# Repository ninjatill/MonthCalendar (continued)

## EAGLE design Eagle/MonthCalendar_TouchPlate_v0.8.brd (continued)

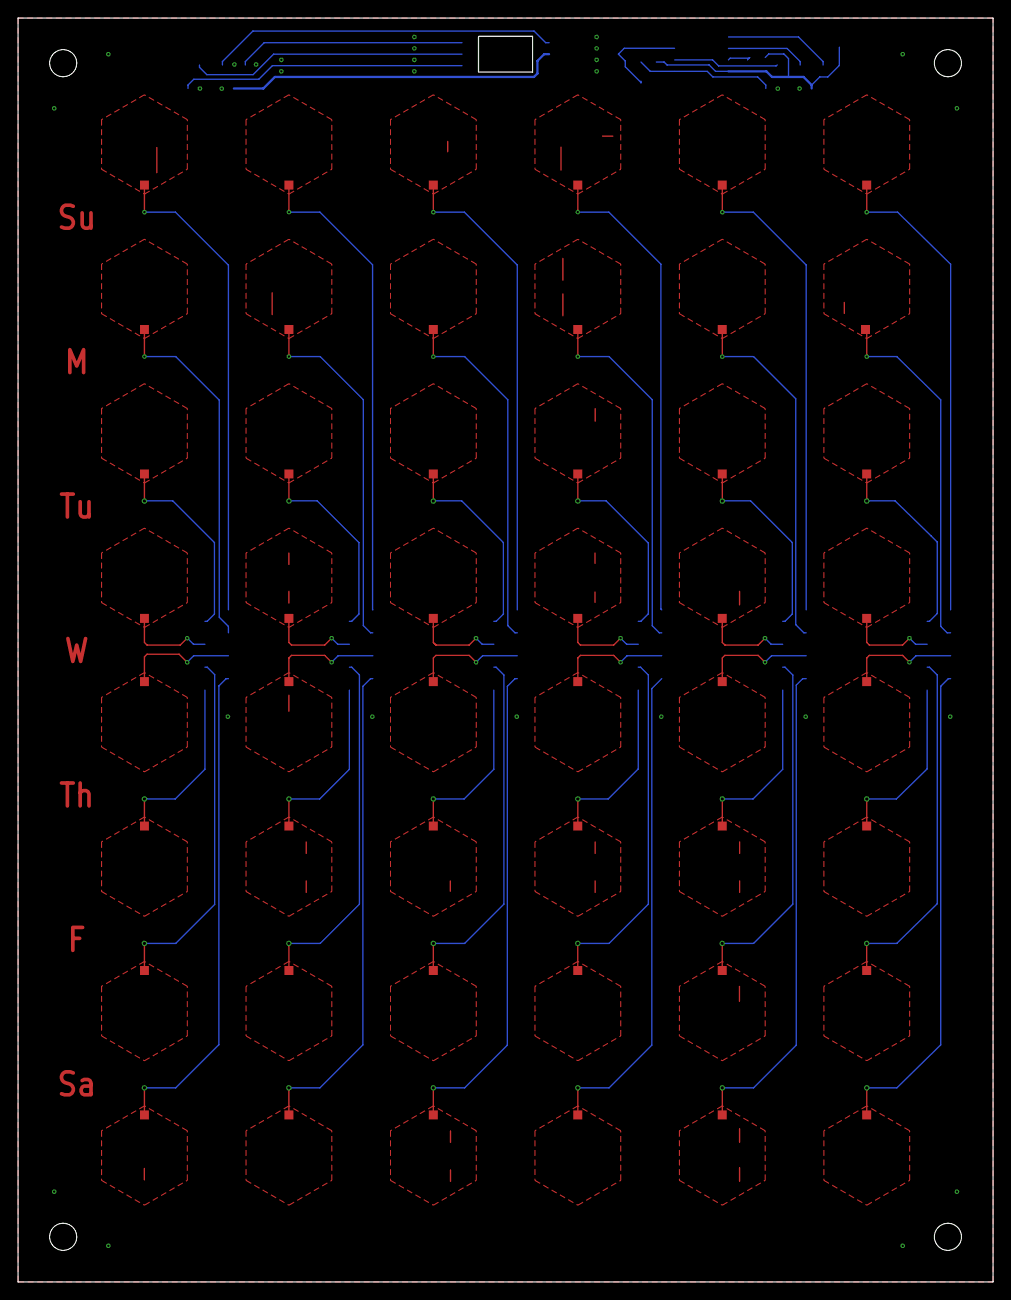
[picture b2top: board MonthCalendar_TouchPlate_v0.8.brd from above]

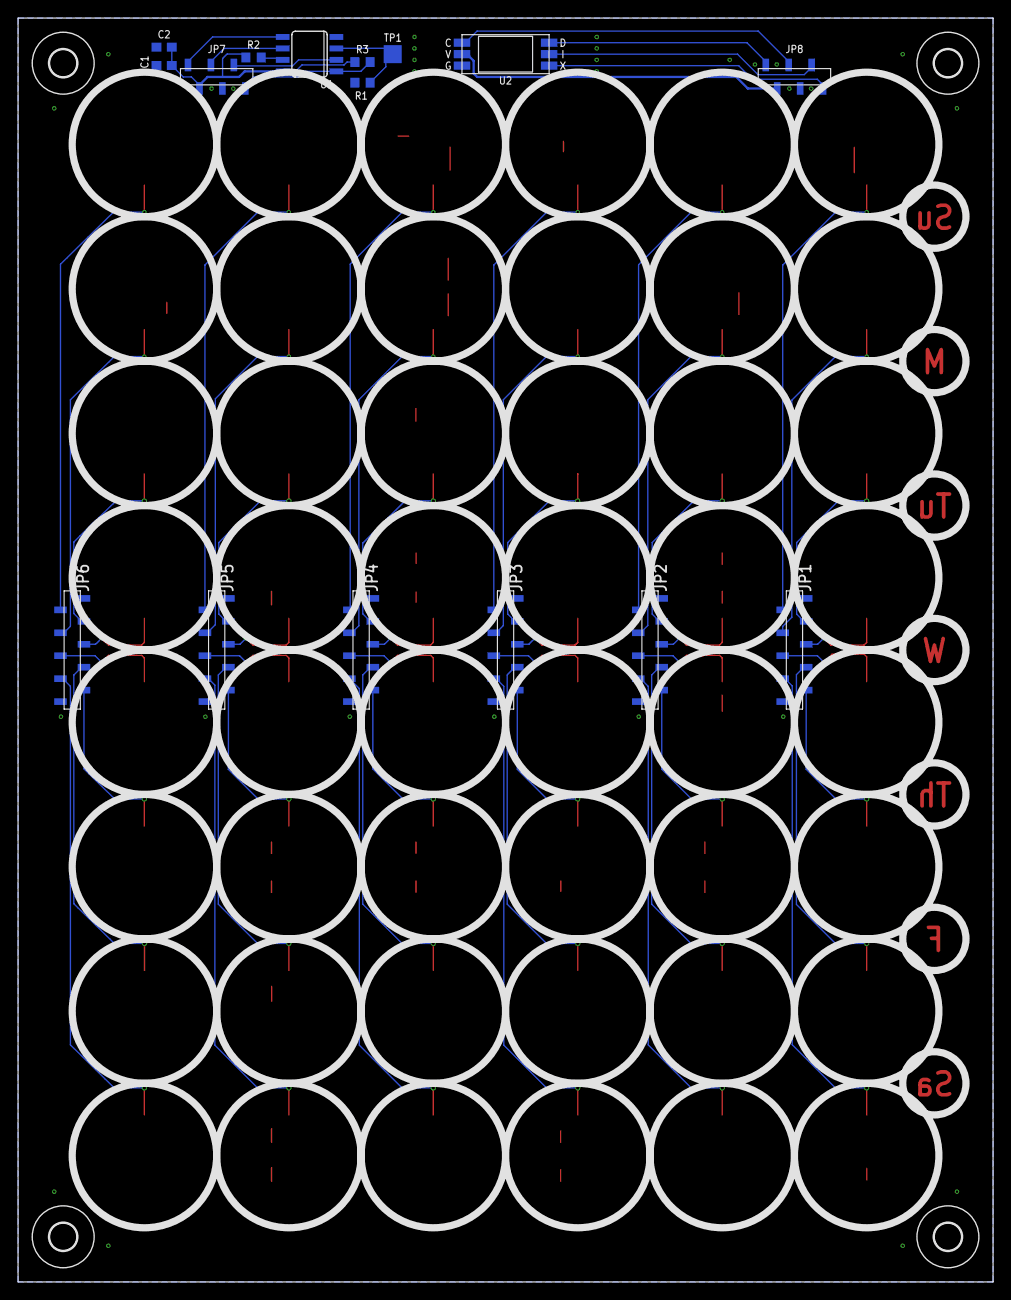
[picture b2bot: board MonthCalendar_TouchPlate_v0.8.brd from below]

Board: 2 copper layers, 108.0 x 140.0 mm, 68 parts (20 on the bottom side), 61 nets.

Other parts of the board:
HOLE_TL: 3,0
U$50, U$51, U$52: 3,0

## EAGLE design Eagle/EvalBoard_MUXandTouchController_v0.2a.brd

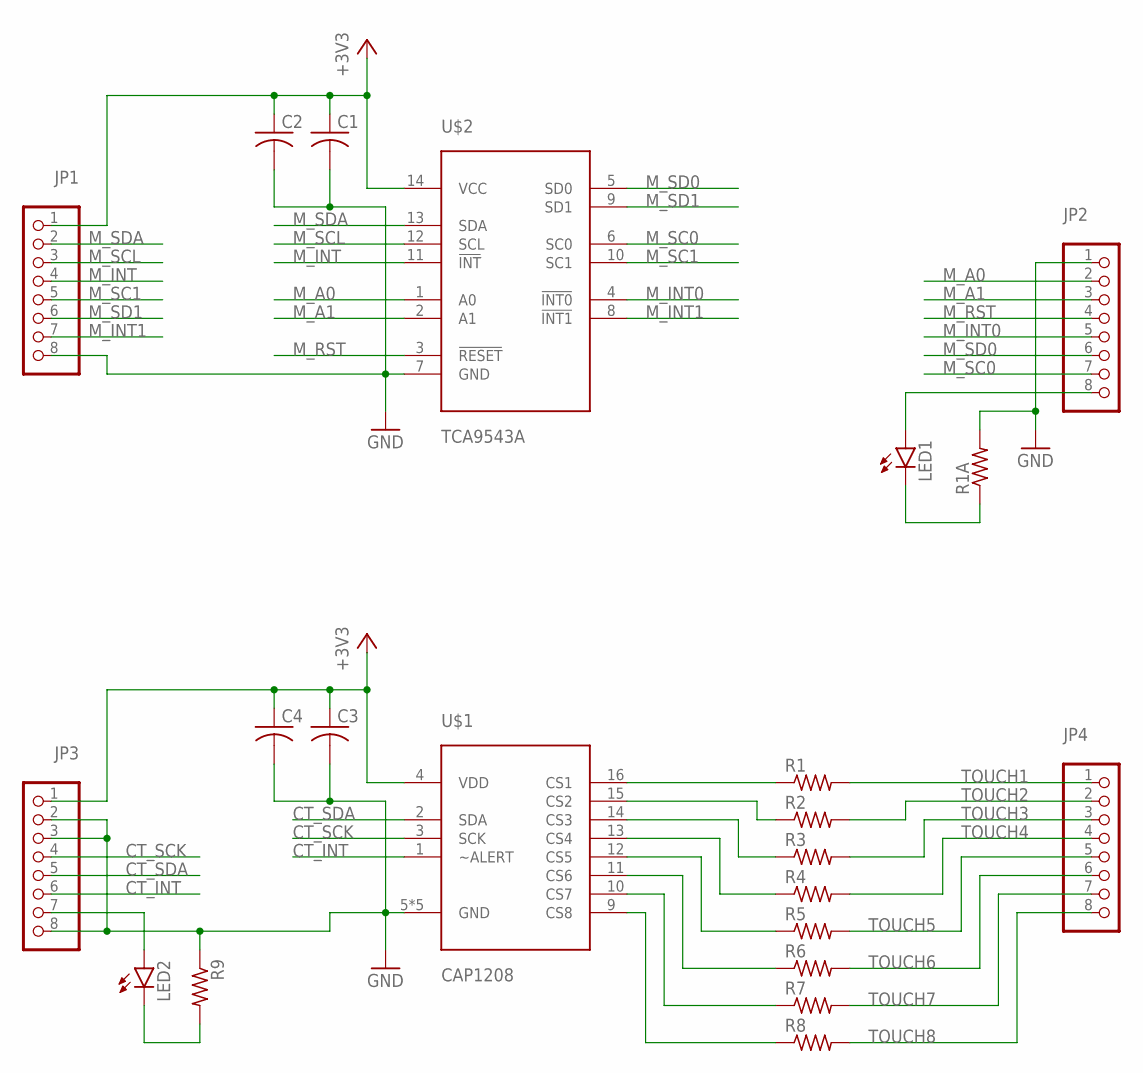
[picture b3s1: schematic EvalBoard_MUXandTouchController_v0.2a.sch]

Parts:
C1, C2, C3, C4: C-USC0603; C0603
JP1, JP2, JP3, JP4: PINHD-1X8BIG; 1X08-BIG
LED1, LED2: LEDCHIP-LED0603; CHIP-LED0603
R1, R1A, R2, R3, R4, R5, R6, R7, R8, R9: R-US_R0603; R0603
U$1: CAP1208; QFN-16-3X3
U$2: TCA9543A; TSSOP-14

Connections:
+3V3: C1.1, C2.1, C3.1, C4.1, JP1.1, JP3.1, U$1.4 (VDD), U$2.14 (VCC)
CT_INT: JP3.6, U$1.1 (~ALERT)
CT_SCK: JP3.4, U$1.3 (SCK)
CT_SDA: JP3.5, U$1.2 (SDA)
GND: C1.2, C2.2, C3.2, C4.2, JP1.8, JP2.1, JP3.2, JP3.3, JP3.8, R1A.2, R9.1, U$1.5 (GND), U$1.6 (GND), U$1.7 (GND), U$1.8 (GND), U$1.PAD (GND), U$2.7 (GND)
M_A0: JP2.2, U$2.1 (A0)
M_A1: JP2.3, U$2.2 (A1)
M_INT: JP1.4, U$2.11 (!INT)
M_INT0: JP2.5, U$2.4 (!INT0)
M_INT1: JP1.7, U$2.8 (!INT1)
M_RST: JP2.4, U$2.3 (!RESET)
M_SC0: JP2.7, U$2.6 (SC0)
M_SC1: JP1.5, U$2.10 (SC1)
M_SCL: JP1.3, U$2.12 (SCL)
M_SD0: JP2.6, U$2.5 (SD0)
M_SD1: JP1.6, U$2.9 (SD1)
M_SDA: JP1.2, U$2.13 (SDA)
unnamed: R1.1, U$1.16 (CS1)
unnamed: JP3.7, LED2.A
unnamed: R2.1, U$1.15 (CS2)
unnamed: LED2.C, R9.2
unnamed: JP2.8, LED1.A
unnamed: LED1.C, R1A.1
unnamed: R3.1, U$1.14 (CS3)
unnamed: R4.1, U$1.13 (CS4)
unnamed: R5.1, U$1.12 (CS5)
unnamed: R6.1, U$1.11 (CS6)
unnamed: R7.1, U$1.10 (CS7)
unnamed: R8.1, U$1.9 (CS8)
TOUCH1: JP4.1, R1.2
TOUCH2: JP4.2, R2.2
TOUCH3: JP4.3, R3.2
TOUCH4: JP4.4, R4.2
TOUCH5: JP4.5, R5.2
TOUCH6: JP4.6, R6.2
TOUCH7: JP4.7, R7.2
TOUCH8: JP4.8, R8.2

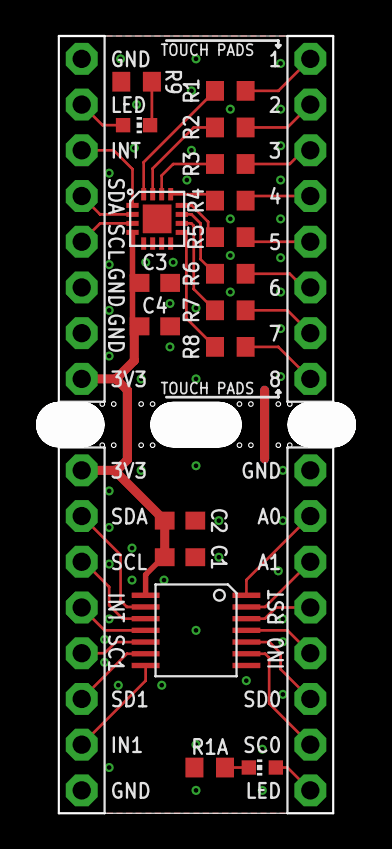
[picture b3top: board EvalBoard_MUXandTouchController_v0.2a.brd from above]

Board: 2 copper layers, 15.2 x 43.2 mm, 22 parts (0 on the bottom side), 37 nets.

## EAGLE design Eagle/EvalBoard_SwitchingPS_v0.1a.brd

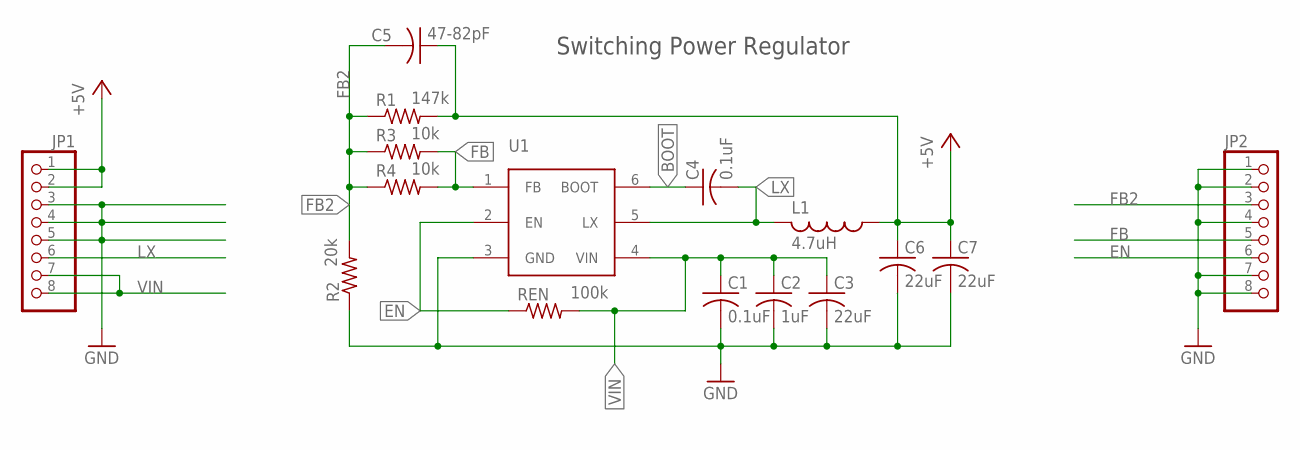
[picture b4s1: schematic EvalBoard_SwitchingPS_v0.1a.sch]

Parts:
C1, C4: 0.1uF; C0603
C2: 1uF; C0603
C3, C6, C7: 22uF; C1206
C5: 47-82pF; C0603
JP1, JP2: PINHD-1X8BIG; 1X08-BIG
L1: 4.7uH; 0207/15
R1: 147k; R0603
R2: 20k; R0603
R3, R4: 10k; R0603
REN: 100k; R0603
U1: RT6255AHGJ6FCT-ND; SOT-23-6

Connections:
+5V: C5.1, C6.1, C7.1, JP1.1, JP1.2, L1.1, R1.2
BOOT: C4.1, U1.6 (BOOT)
EN: JP2.6, REN.1, U1.2 (EN)
FB: JP2.5, R3.2, R4.2, U1.1 (FB)
FB2: C5.2, JP2.3, R1.1, R2.2, R3.1, R4.1
GND: C1.2, C2.2, C3.2, C6.2, C7.2, JP1.3, JP1.4, JP1.5, JP2.1, JP2.2, JP2.4, JP2.7, JP2.8, R2.1, U1.3 (GND)
LX: C4.2, JP1.6, L1.2, U1.5 (LX)
VIN: C1.1, C2.1, C3.1, JP1.7, JP1.8, REN.2, U1.4 (VIN)

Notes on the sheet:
Switching Power Regulator

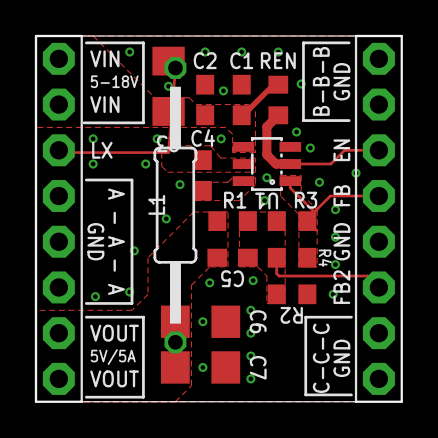
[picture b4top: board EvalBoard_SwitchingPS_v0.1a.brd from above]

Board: 2 copper layers, 20.3 x 20.3 mm, 16 parts (0 on the bottom side), 8 nets.

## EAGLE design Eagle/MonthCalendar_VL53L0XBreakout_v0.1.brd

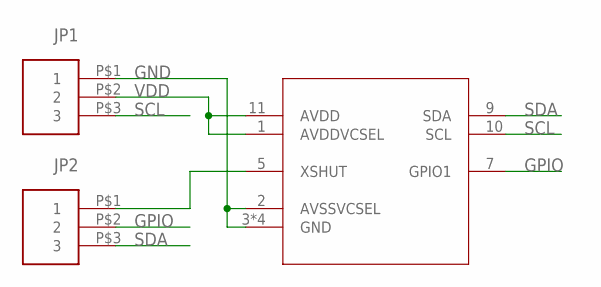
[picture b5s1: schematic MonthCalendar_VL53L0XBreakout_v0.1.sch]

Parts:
JP1, JP2: PINHEAD_1X350MIL; PINHEAD_1X3_50MIL
U1: VL53L0X

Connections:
GND: JP1.P$1 (1), U1.2 (AVSSVCSEL), U1.3 (GND), U1.4 (GND), U1.6 (GND), U1.12 (GND)
GPIO: JP2.P$2 (2), U1.7 (GPIO1)
SCL: JP1.P$3 (3), U1.10 (SCL)
SDA: JP2.P$3 (3), U1.9 (SDA)
VDD: JP1.P$2 (2), U1.1 (AVDDVCSEL), U1.11 (AVDD)
XSHUT: JP2.P$1 (1), U1.5 (XSHUT)

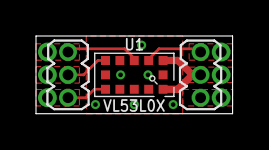
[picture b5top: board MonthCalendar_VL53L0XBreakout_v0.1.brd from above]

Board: 2 copper layers, 10.9 x 4.3 mm, 3 parts (0 on the bottom side), 6 nets.

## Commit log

2019-05-30 Initial Commit
    Initial Commit
2019-06-18 Initial Commit
    Added all v0.x files for controller, touch plate and evaluation breadout boards.
2019-06-18 Added development warning.
    Added development warning.
2019-06-18 Added controller files v0.9
    Added controller files v0.9
